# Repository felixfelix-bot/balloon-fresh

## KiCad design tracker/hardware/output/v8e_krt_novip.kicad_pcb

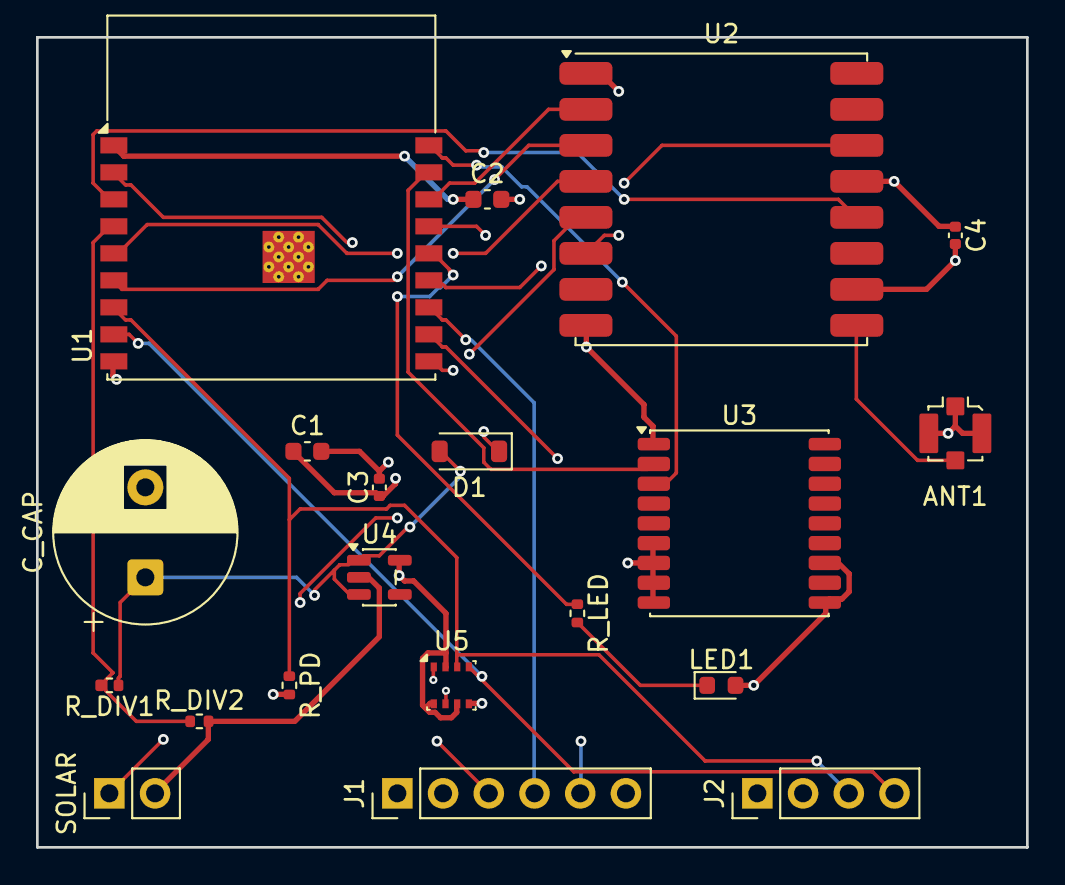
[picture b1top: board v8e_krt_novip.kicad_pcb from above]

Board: 4 copper layers, 55.0 x 45.0 mm, 20 parts (0 on the bottom side), 22 nets.

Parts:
ANT1: U.FL; U.FL_Molex_MCRF_73412-0110_Vertical
C1, C2: 10uF; C_0603_1608Metric
C3, C4: 100nF; C_0402_1005Metric
C_CAP: 1F_5.5V; CP_Radial_D10.0mm_P5.00mm
D1: BAT54; D_SOD-123
J1: Prog_Header; PinHeader_1x06_P2.54mm_Vertical
J2: Debug_Header; PinHeader_1x04_P2.54mm_Vertical
LED1: LED_RED; LED_0603_1608Metric
R_DIV1, R_DIV2: 100k; R_0402_1005Metric
R_LED: 330R; R_0402_1005Metric
R_PD: 10k; R_0402_1005Metric
SOLAR: Solar_In; PinHeader_1x02_P2.54mm_Vertical
U1: ESP32-C3-WROOM-02
U2: LR2021F33; HOPERF_RFM9XW_SMD
U3: MAX-M10S; ublox_MAX
U4: TPS7A02; SOT-23-5
U5: BMP280; Bosch_LGA-8_2.5x2.5mm_P0.65mm_ClockwisePinNumbering

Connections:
+3V3: C1.1, C2.1, C3.1, C4.1, J1.2, J2.2, R_PD.2, U1.1, U2.13, U3.6, U3.7, U3.8, U3.9, U4.5, U5.2, U5.6, U5.8
EN: J1.3, U1.2
GND: ANT1.2, C1.2, C2.2, C3.2, C4.2, C_CAP.2, J1.1, J2.1, LED1.2, R_DIV2.2, SOLAR.2, U1.9, U1.19, U2.1, U2.8, U2.10, U3.1, U3.10, U3.12, U4.2, U5.1, U5.5, U5.7
GPS_RX: U1.17, U3.2
GPS_TX: U1.18, U3.3
I2C_SCL: J2.4, U1.8, U5.4
I2C_SDA: J2.3, R_PD.1, U1.7, U5.3
LED_A: LED1.1, R_LED.2
LED_DRIVE: R_LED.1, U1.14
LR_BUSY: U1.3, U2.12
LR_DIO0: U1.13, U2.14
LR_RST: U1.15, U2.6
RF_OUT: ANT1.1, U2.9
SOLAR_IN: D1.1, SOLAR.1
SPI_MISO: U1.16, U2.2
SPI_MOSI: U1.6, U2.3
SPI_NSS: U1.10, U2.5
SPI_SCK: U1.5, U2.4
UART0_RX: J1.5, U1.11
UART0_TX: J1.4, U1.12
VCAP: C_CAP.1, D1.2, R_DIV1.1, U4.1, U4.3
VDIV_MID: R_DIV1.2, R_DIV2.1, U1.4

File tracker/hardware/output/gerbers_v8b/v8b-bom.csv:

Comment,Designator,Footprint,Layer,Qty
U.FL,ANT1,U.FL_Molex_MCRF_73412-0110_Vertical,top,1
10uF,C1,C_0603_1608Metric,top,1
10uF,C2,C_0603_1608Metric,top,1
100nF,C3,C_0402_1005Metric,top,1
100nF,C4,C_0402_1005Metric,top,1
1F_5.5V,C_CAP,CP_Radial_D10.0mm_P5.00mm,top,1
BAT54,D1,D_SOD-123,top,1
Prog_Header,J1,PinHeader_1x06_P2.54mm_Vertical,top,1
Debug_Header,J2,PinHeader_1x04_P2.54mm_Vertical,top,1
LED_RED,LED1,LED_0603_1608Metric,top,1
100k,R_DIV1,R_0402_1005Metric,top,1
100k,R_DIV2,R_0402_1005Metric,top,1
330R,R_LED,R_0402_1005Metric,top,1
10k,R_PD,R_0402_1005Metric,top,1
Solar_In,SOLAR,PinHeader_1x02_P2.54mm_Vertical,top,1
ESP32-C3-WROOM-02,U1,ESP32-C3-WROOM-02,top,1
LR2021F33,U2,HOPERF_RFM9XW_SMD,top,1
MAX-M10S,U3,ublox_MAX,top,1
TPS7A02,U4,SOT-23-5,top,1
BMP280,U5,Bosch_LGA-8_2.5x2.5mm_P0.65mm_ClockwisePinNumbering,top,1
